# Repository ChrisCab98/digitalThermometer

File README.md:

# digitalThermometer
Digital thermometer based on ESP8266 - MQTT - influxDB - Grafana

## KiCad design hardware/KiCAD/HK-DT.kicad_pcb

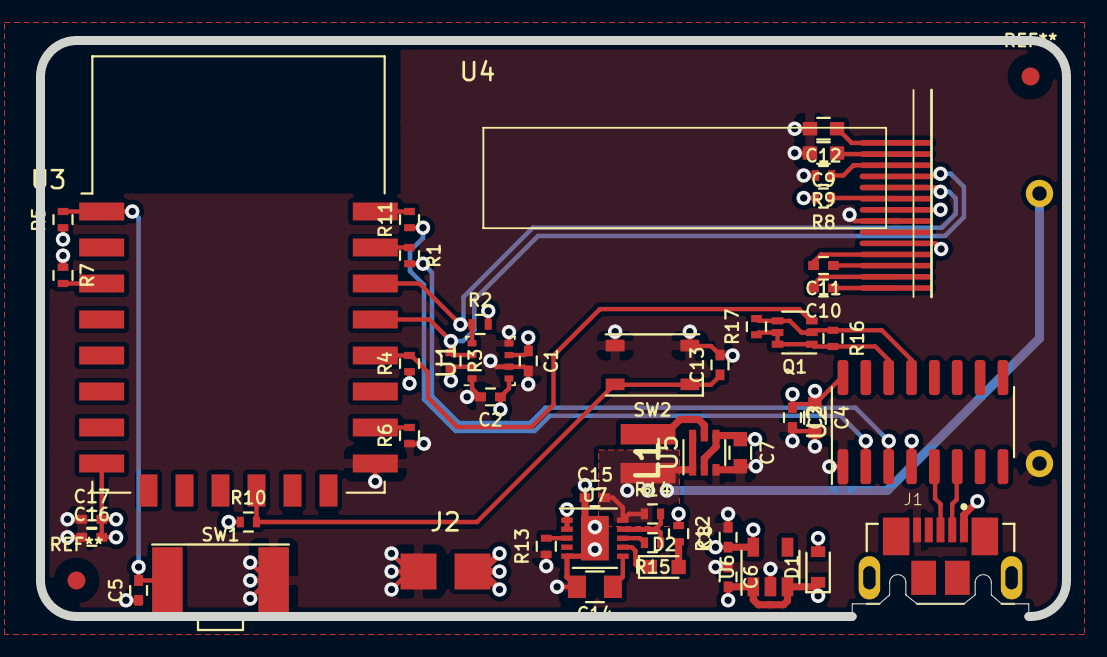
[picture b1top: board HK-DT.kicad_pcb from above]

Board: 4 copper layers, 57.0 x 32.0 mm, 50 parts (1 on the bottom side), 35 nets.

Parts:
BT1: Battery; 2462
C1, C2, C3, C5, C13, C16, C17: C_0002; C_0402
C4, C7, C9, C12: C_0003; C_0603
C6, C15: C_0044; C_0402
C8, C10, C11: C_0045; C_0402
C14: C_0060; C_0805
D1: D_0020; D_0603
D2: D_0001; LED_0603-red
J1: USB_B_Micro; MOLEX_105164-0001
J2: Pad_1x2; DualPad
L1: L_0004; LPS3015
Q1: Q_0001; SOT_363-SC_70-6
R1, R11: 470; R_0402
R2, R3: 4.7k; R_0402
R4, R5, R6, R7, R10, R16, R17: 10k; R_0402
R8: R_0020; R_0402
R9: 390k; R_0402
R12: R_0005; R_0402
R13: R_0140; R_0402
R14: 324k; R_0402
R15: 178k; R_0402
SW1: SW_0002; KSS221G
SW2: SW_0003; PTS810
U1: BME280; Bosch_LGA-8_2.5x2.5mm_P0.65mm_ClockwisePinNumbering
U2: CH340G; SOIC-16_3.9x9.9mm_P1.27mm
U3: ESP-12E
U4: SSD1306; ssd1306
U5: TLV61225; SOT-363_SC-70-6
U6: U_0037; SOT_23-5
U7: U_0104; DFN_10-1EP_3x3mm_P0.5mm

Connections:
+3V3: C1.1, C2.1, C3.1, C4.1, C7.1, C8.1, C16.2, C17.2, R2.2, R3.2, R4.1, R5.1, R7.1, R8.2, R10.1, U1.2, U1.6, U1.8, U2.4, U2.16, U3.8, U4.5, U4.8, U5.2, U5.4, U6.5
+5V: C6.2, D1.1, J2.2, R12.1, U6.1, U6.3, U7.1, U7.2
+BATT: BT1.1, C15.2, L1.1, R14.1, U5.1, U5.6, U7.10
/BP: C13.1, R10.2, SW2.1, SW2.2, U3.12
/D+: J1.3, U2.5
/D-: J1.2, U2.6
/GPIO0: Q1.3, R4.2, U3.18
/RST: C5.2, R5.2, SW1.1, U3.1
/Rx: R1.1, U3.21
/SCL: R2.1, U1.4, U3.20, U4.10
/SDA: R3.1, U1.3, U3.19, U4.11
/Tx: R11.2, U3.22
/~DTR: Q1.2, Q1.4, R16.1, R17.2, U2.13
/~RST: Q1.1, Q1.5, Q1.6, R16.2, R17.1, U2.14
GND: BT1.2, C1.2, C2.2, C3.2, C4.2, C5.1, C6.1, C7.2, C8.2, C9.2, C12.2, C13.2, C14.2, C15.1, C16.1, C17.1, J1.5, J2.1, R6.1, R9.2, R13.1, SW1.2, SW2.3, SW2.4, U1.1, U1.5, U1.7, U2.1, U3.15, U4.7, U5.3, U6.2, U7.5, U7.11
unnamed: C9.1, U4.13
unnamed: C10.1, U4.1
unnamed: C10.2, U4.2
unnamed: C11.1, U4.3
unnamed: C11.2, U4.4
unnamed: C12.1, U4.14
unnamed: C14.1, U7.6
unnamed: D1.2, J1.1
unnamed: D2.1, U7.7
unnamed: D2.2, R12.2
unnamed: L1.2, U5.5
unnamed: R1.2, U2.3
unnamed: R6.2, U3.16
unnamed: R7.2, U3.3
unnamed: R8.1, U4.9
unnamed: R9.1, U4.12
unnamed: R11.1, U2.2
unnamed: R13.2, U7.3
unnamed: R14.2, R15.1, U7.9
unnamed: R15.2, U7.8

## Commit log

2020-02-12 test writting point : ok
2020-02-12 Add BME280 code
2020-02-13 Add OLED code
2020-02-13 move files into folder
2020-02-13 add hardware parts
2020-02-13 move .vscode folder in software folder
2020-02-13 Printing Wifi progress & temperature on OLED
2020-02-14 cleaning schematic / Routing started (Power line mostly done), need to change USB footprint & make 3D Model / Footprint of OLED
2020-02-14 Add BME280 3dModel
2020-03-03 Change footprint USB - Fix OLED Display Footprint
2020-03-03 Add BatteryHolder Footprint & 3D, routing done, need to move power section to left
2020-03-04 Power placement is ok, need to change pinout battery holder
2020-03-05 Change Pads Battery holder, Add decoupling capacitor
